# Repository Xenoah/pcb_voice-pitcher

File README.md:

# Voice Pitcher — standalone audio DSP prototype

**98 × 98 mm、表面のみの部品実装、SSD1306表示器と4つの操作ボタンを備えた音声エフェクターの設計・ファームウェアです。** STM32H743とPCM3060を使い、ステレオライン入出力とUSB-Cオーディオを切り替えます。

現在は **Rev 0.1の未実機検証プロトタイプ** です。回路図ERC・基板DRC・未接続はすべて0件、回路図とPCBの端子接続も照合済みです。実機の起動、USB互換性、音質、遅延、消費電流、温度は未測定です。添付データは試作レビュー用で、量産承認済みではありません。

## ダウンロード

- [全データ ZIP](downloads/voice_pitcher_rev0.1_prototype.zip?raw=true) — 回路図、PCB、製造データ、ファームウェア、説明書、検証記録
- [ガーバー・ドリル ZIP](downloads/voice_pitcher_gerbers.zip?raw=true)
- [JLCPCB用 BOM](downloads/jlc_bom.csv?raw=true) / [CPL](downloads/jlc_cpl.csv?raw=true) / [調達状況付き全BOM](downloads/bom_master.csv?raw=true)
- [日本語説明書 PDF](downloads/voice_pitcher_manual_ja.pdf?raw=true) / [回路図 PDF](downloads/schematic.pdf?raw=true) / [表面実装図 PDF](downloads/assembly-top.pdf?raw=true)
- [ファームウェア BIN](downloads/firmware/voice_pitcher.bin?raw=true) / [HEX](downloads/firmware/voice_pitcher.hex?raw=true) / [ELF](downloads/firmware/voice_pitcher.elf?raw=true)
- [検証結果](downloads/reports/hardware.json) / [DSP周波数テスト](downloads/reports/dsp-spectral.json) / [SHA-256](downloads/SHA256SUMS.txt)
- [スクリーンショット全18枚 ZIP](downloads/voice_pitcher_screenshots.zip?raw=true) / [画像付きプレリリース](https://github.com/Xenoah/pcb_voice-pitcher/releases/tag/v0.1.0-prototype)

CSVはページ右上のDownload raw file、ZIPは上記リンクから保存できます。BOMの空欄LCSC番号は未確定部品です。注文前に [製造手順](docs/manufacturing.md) の照合が必要です。

## スクリーンショット

実際のKiCadデータとPDFから出力した設計画面です。実機写真ではありません。3Dモデル未提供のJ1（USB-C）、J2/J3（音声ジャック）、Y1（発振器）、および外付けOLEDは3D表示に含まれません。

**3D斜視** — 98 × 98 mm、全ての部品を表面に実装する設計。

**表裏・4層の一覧** — 上段は3D表裏、中段は表裏配線、下段はGND / 3.3 V内層。裏面図は裏側から見た向きです。

**回路図全7ページと説明書** — 全体構成、MCU、電源、USB、コーデック、アナログ、表示・操作回路。

<details>
<summary>個別の高解像度画像を表示</summary>

|3D表面|3D裏面|
|---|---|
|||
|表面配線|裏面配線|
|||
|L2 GND|L3 3.3 V|
|||
|実装図|回路図：全体|
|||
|回路図：MCU|回路図：電源|
|||
|回路図：USB-C|回路図：コーデック|
|||
|回路図：アナログ|回路図：OLED・スイッチ|
|||
|日本語説明書・先頭ページ|画像の生成元|
||[CADハッシュ・3Dモデル出典・画像一覧](downloads/screenshots/manifest.json)|

</details>

画像を再生成する場合は `python3 tools/render_gallery.py --fetch-models` を実行します。KiCad 9、Inkscape、poppler-utils、Python Pillow/reportlabが必要です。

## 設計内容

|項目|Rev 0.1の内容|
|---|---|
|基板|98 × 98 mm、4層、部品は全てTOP。片面実装であり、片面銅箔基板ではありません|
|処理|STM32H743VIT6、400 MHz、32 bit float DSP、24 bit / 48 kHzステレオ|
|変換|PCM3060PWR、独立したADC/DAC、アナログ5 V・デジタル3.3 V|
|アナログ端子|入力・出力各1個の3.5 mm TRSステレオライン。6.35 mmは外付け変換アダプタ|
|USB-C|USB 2.0 Full Speed、UAC2のデバイス。PC・スマホ側がホスト|
|ルーティング|LINE→LINE、LINE→USB、USB→LINE、USB→USB|
|操作|SSD1306 128×64 I²C、MODE / DOWN / UP / I/O、別途RESET / BOOT|
|エフェクト|DRY、±12半音ピッチ変更、単音ピッチ補正、500 msディレイ、5 Hzトレモロ|
|スタンドアローン|PC不要のLINE→LINE動作。5 Vで1.5 A以上を広告するType-C電源を想定|
|調達|抵抗と100 nFを中心にJLCPCB Basicへ寄せた構成。全品Basicではありません|

**ピッチ変更を「音質ロスゼロ・遅延ゼロ」で行うことはできません。** 音程推定には観測時間が必要で、ADC/DAC・バッファにも遅延があります。本設計は専用基板上のMCUでリアルタイム処理します。無加工デジタルDRYは24 bit整数の往復一致をテスト済みですが、アナログ往復やピッチ処理の無損失を意味しません。

DRYのアナログ往復は計算上約2.1 msを起点とする設計です。ピッチ処理は可変遅延約1.3–65.3 ms、音程検出は約42.7 msの窓に分割演算と追従時間が加わります。USB経路はさらにホストのバッファに依存します。いずれも実測保証値ではありません。

## 使い方と設計資料

1. [ハードウェア仕様・ピン配置](docs/hardware.md)
2. [ファームウェア・操作・ビルド](docs/firmware.md)
3. [JLCPCB製造・部品調達](docs/manufacturing.md)
4. [検証済み範囲と実機チェック](docs/validation.md)
5. [データシートと依存ライブラリ](docs/sources.md)

通常のマイク、パッシブギター、ヘッドホンを直接つなぐための回路ではありません。マイクには外部プリアンプ、楽器には適切なバッファ、ヘッドホンには外部アンプを使用してください。USBホスト機能はないため、別のUSBオーディオインターフェースを本機へ直接接続する構成には対応しません。

KiCad 9で [hardware/voice_pitcher.kicad_pro](hardware/voice_pitcher.kicad_pro) を開けます。配線済みPCBは `voice_pitcher.kicad_pcb` です。`placement.kicad_pcb` は再配置・再配線用の中間ファイルです。

```sh
bash tools/bootstrap.sh
make test
make firmware
make hardware-check
make exports
python3 tools/package_release.py
```

必要なツールとインストール方法は [ビルド手順](docs/firmware.md) を参照してください。オリジナルコード・設計はMIT、同梱KiCadライブラリと外部依存物にはそれぞれのライセンスが適用されます。

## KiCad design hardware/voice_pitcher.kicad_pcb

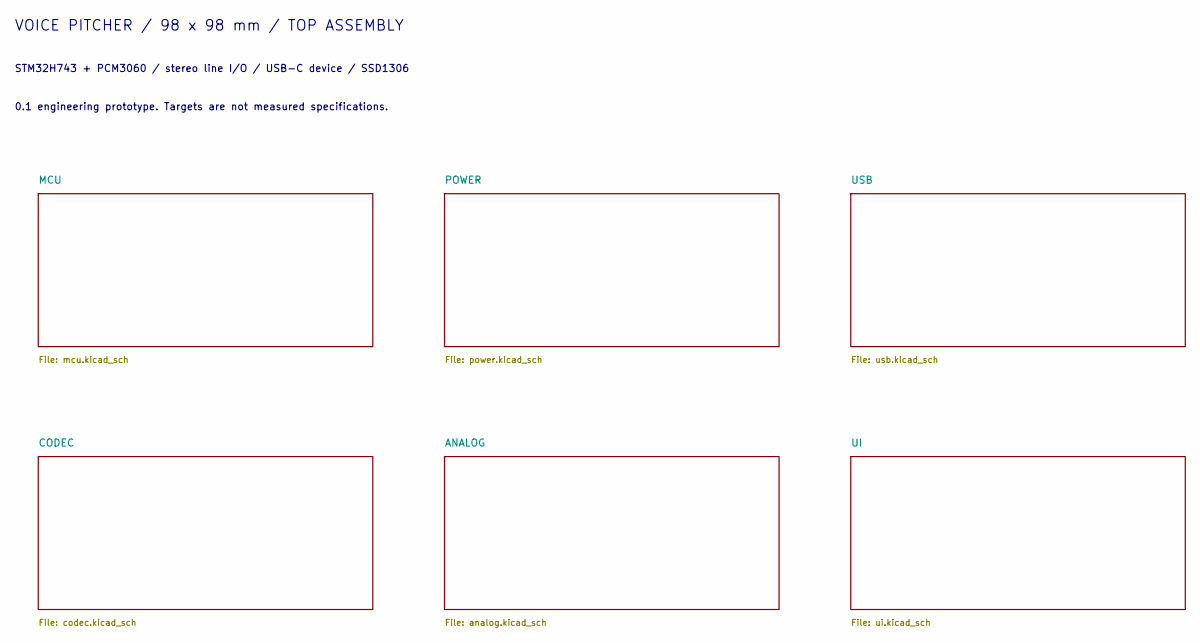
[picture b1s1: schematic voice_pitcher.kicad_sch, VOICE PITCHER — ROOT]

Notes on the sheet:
VOICE PITCHER / 98 x 98 mm / TOP ASSEMBLY
STM32H743 + PCM3060 / stereo line I/O / USB-C device / SSD1306
0.1 engineering prototype. Targets are not measured specifications.

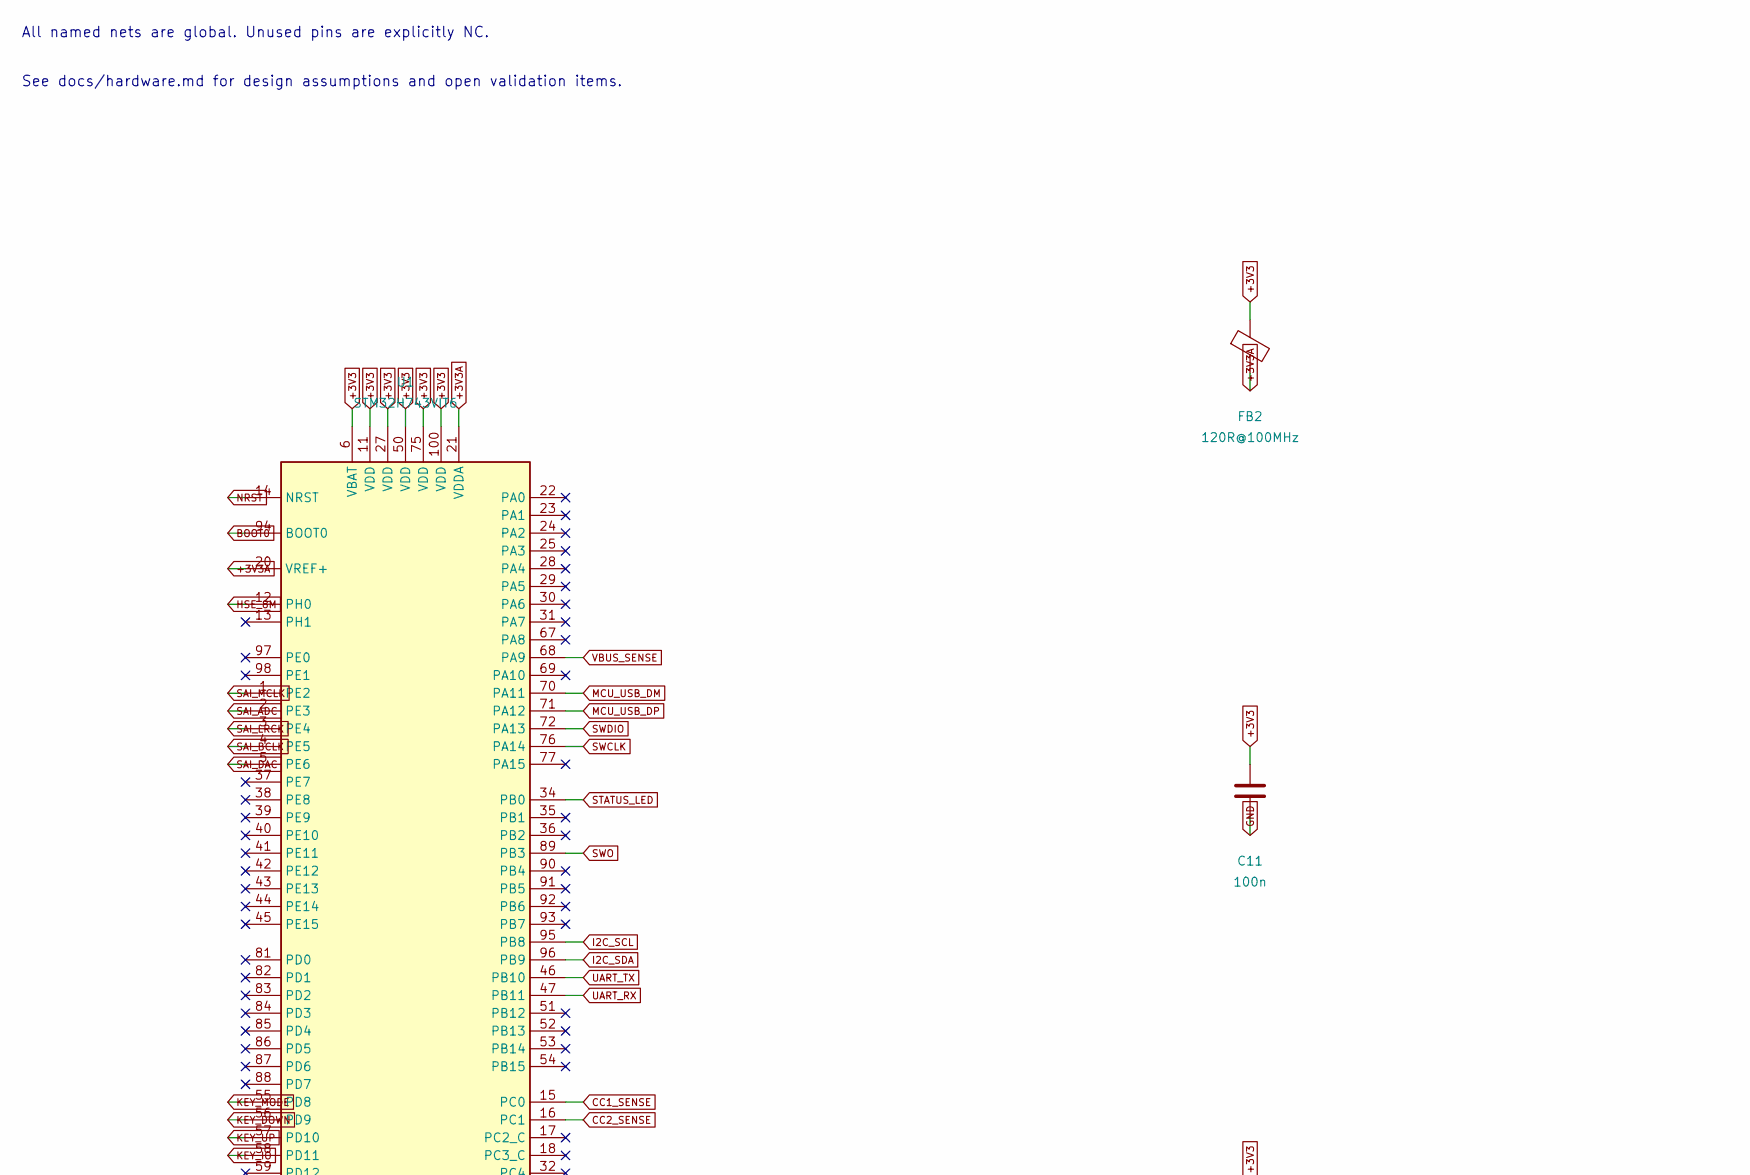
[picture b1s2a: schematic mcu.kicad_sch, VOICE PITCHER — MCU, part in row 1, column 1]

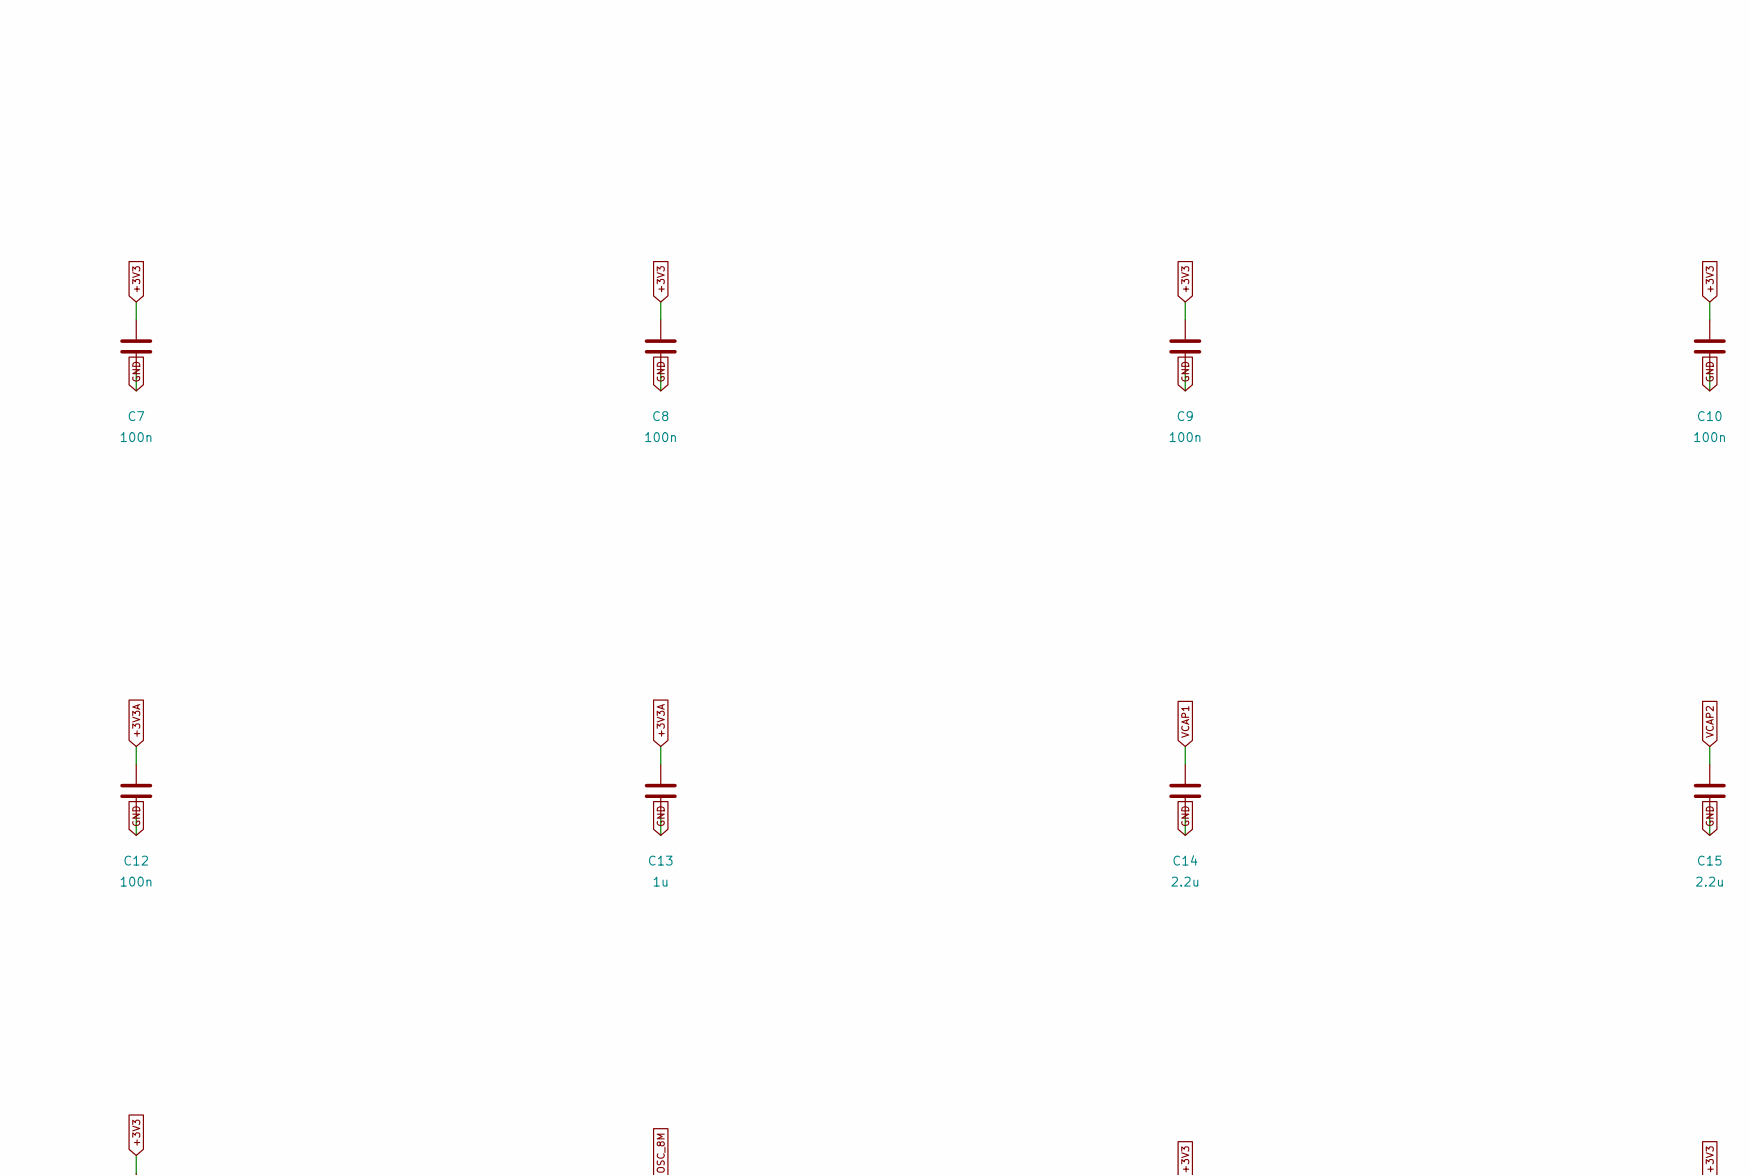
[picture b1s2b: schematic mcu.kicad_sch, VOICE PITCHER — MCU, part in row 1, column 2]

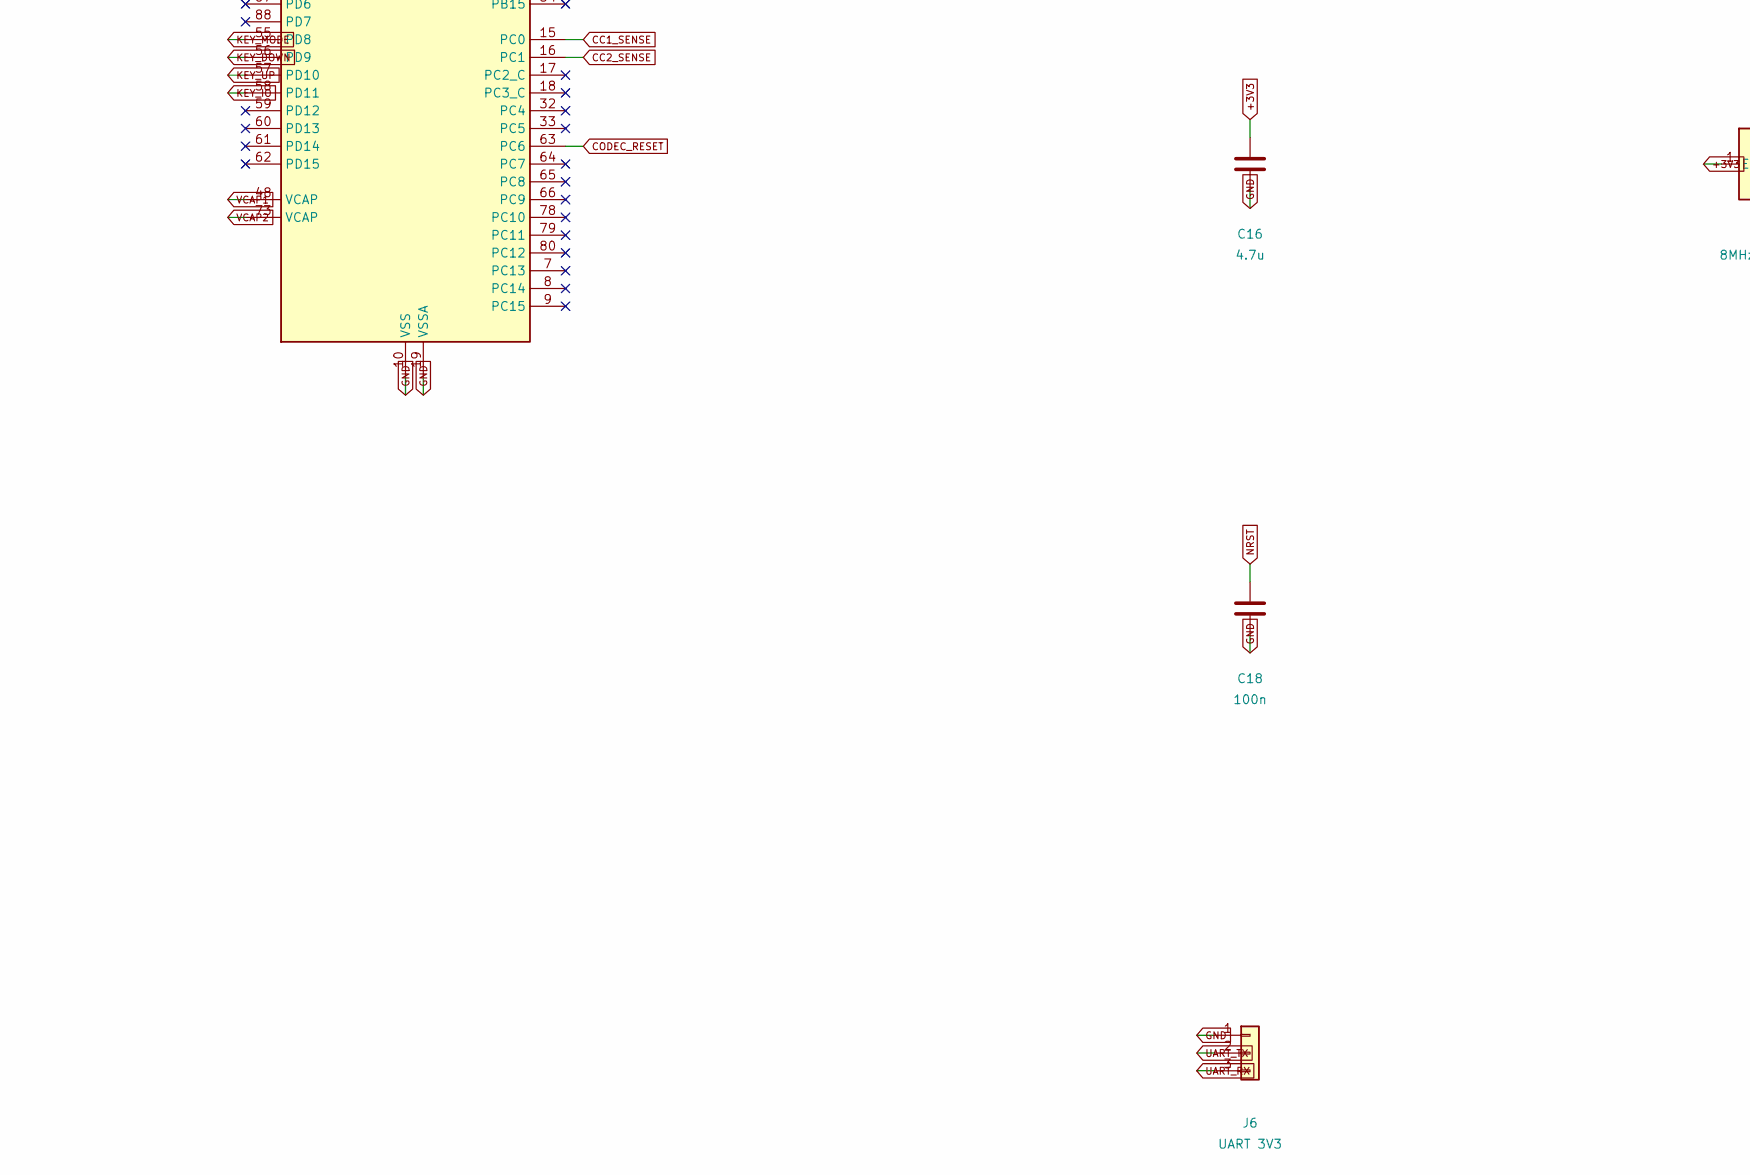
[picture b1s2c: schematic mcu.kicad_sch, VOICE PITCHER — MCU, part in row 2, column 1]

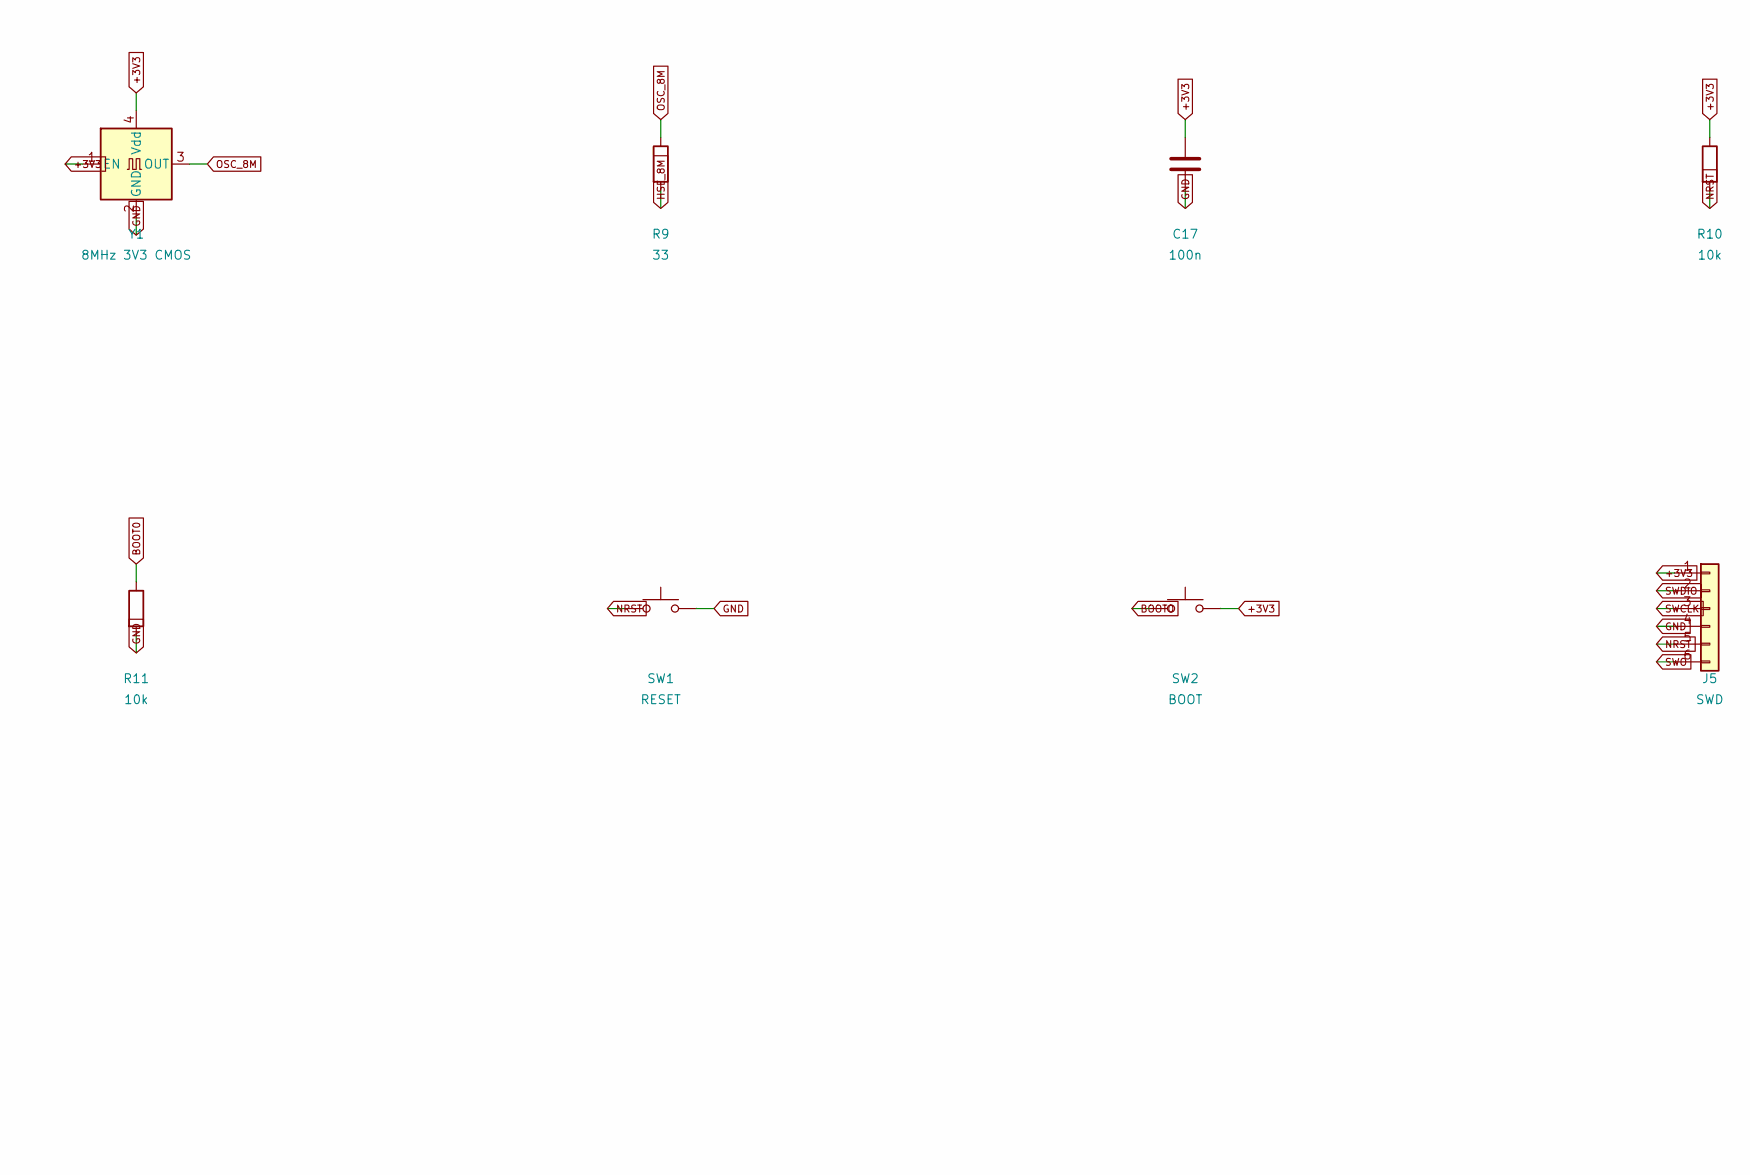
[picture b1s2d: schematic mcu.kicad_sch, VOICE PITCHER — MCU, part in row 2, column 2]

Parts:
C7, C8, C9, C10, C11, C12, C17, C18: 100n; Capacitor_SMD__C_0603_1608Metric; MPN CC0603KRX7R9BB104; LCSC C14663
C13: 1u; Capacitor_SMD__C_0603_1608Metric; MPN GRM188R71C105KA12D
C14, C15: 2.2u; Capacitor_SMD__C_0603_1608Metric; MPN GRM188R61C225KE15D
C16: 4.7u; Capacitor_SMD__C_0603_1608Metric; MPN GRM188R61C475KE11D
FB2: 120R@100MHz; Inductor_SMD__L_0805_2012Metric; MPN BLM21PG121SN1D
J5: SWD; Connector_PinHeader_2.54mm__PinHeader_1x06_P2.54mm_Vertical; MPN 1x6 2.54mm header
J6: UART 3V3; Connector_PinHeader_2.54mm__PinHeader_1x03_P2.54mm_Vertical; MPN 1x3 2.54mm header
R9: 33; Resistor_SMD__R_0603_1608Metric; MPN 0603WAF330JT5E; LCSC C23140
R10, R11: 10k; Resistor_SMD__R_0603_1608Metric; MPN 0603WAF1002T5E; LCSC C25804
SW1: RESET; Button_Switch_SMD__SW_SPST_TL3342; MPN TL3342F160QG
SW2: BOOT; Button_Switch_SMD__SW_SPST_TL3342; MPN TL3342F160QG
U1: STM32H743VIT6; Package_QFP__LQFP-100_14x14mm_P0.5mm; MPN STM32H743VIT6; LCSC C114409
Y1: 8MHz 3V3 CMOS; Oscillator__Oscillator_SMD_Abracon_ASE-4Pin_3.2x2.5mm; MPN ASE-8.000MHZ-LC-T

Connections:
+3V3: C7.1, C8.1, C9.1, C10.1, C11.1, C16.1, C17.1, FB2.1, J5.1, R10.1, SW2.2, U1.6 (VBAT), U1.11 (VDD), U1.27 (VDD), U1.50 (VDD), U1.75 (VDD), U1.100 (VDD), Y1.1 (EN), Y1.4 (Vdd); also elsewhere on the board
+3V3A: C12.1, C13.1, FB2.2, U1.20 (VREF+), U1.21 (VDDA)
BOOT0: R11.1, SW2.1, U1.94 (BOOT0)
CC1_SENSE: U1.15 (PC0); also elsewhere on the board
CC2_SENSE: U1.16 (PC1); also elsewhere on the board
CODEC_RESET: U1.63 (PC6); also elsewhere on the board
GND: C7.2, C8.2, C9.2, C10.2, C11.2, C12.2, C13.2, C14.2, C15.2, C16.2, C17.2, C18.2, J5.4, J6.1, R11.2, SW1.2, U1.10 (VSS), U1.19 (VSSA), U1.26 (VSS), U1.49 (VSS), U1.74 (VSS), U1.99 (VSS), Y1.2 (GND); also elsewhere on the board
HSE_8M: R9.2, U1.12 (PH0)
I2C_SCL: U1.95 (PB8); also elsewhere on the board
I2C_SDA: U1.96 (PB9); also elsewhere on the board
KEY_DOWN: U1.56 (PD9); also elsewhere on the board
KEY_IO: U1.58 (PD11); also elsewhere on the board
KEY_MODE: U1.55 (PD8); also elsewhere on the board
KEY_UP: U1.57 (PD10); also elsewhere on the board
MCU_USB_DM: U1.70 (PA11); also elsewhere on the board
MCU_USB_DP: U1.71 (PA12); also elsewhere on the board
NRST: C18.1, J5.5, R10.2, SW1.1, U1.14 (NRST)
OSC_8M: R9.1, Y1.3 (OUT)
SAI_ADC: U1.2 (PE3); also elsewhere on the board
SAI_BCLK: U1.4 (PE5); also elsewhere on the board
SAI_DAC: U1.5 (PE6); also elsewhere on the board
SAI_LRCK: U1.3 (PE4); also elsewhere on the board
SAI_MCLK: U1.1 (PE2); also elsewhere on the board
STATUS_LED: U1.34 (PB0); also elsewhere on the board
SWCLK: J5.3, U1.76 (PA14)
SWDIO: J5.2, U1.72 (PA13)
SWO: J5.6, U1.89 (PB3)
UART_RX: J6.3, U1.47 (PB11)
UART_TX: J6.2, U1.46 (PB10)
VBUS_SENSE: U1.68 (PA9); also elsewhere on the board
VCAP1: C14.1, U1.48 (VCAP)
VCAP2: C15.1, U1.73 (VCAP)

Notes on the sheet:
All named nets are global. Unused pins are explicitly NC.
See docs/hardware.md for design assumptions and open validation items.

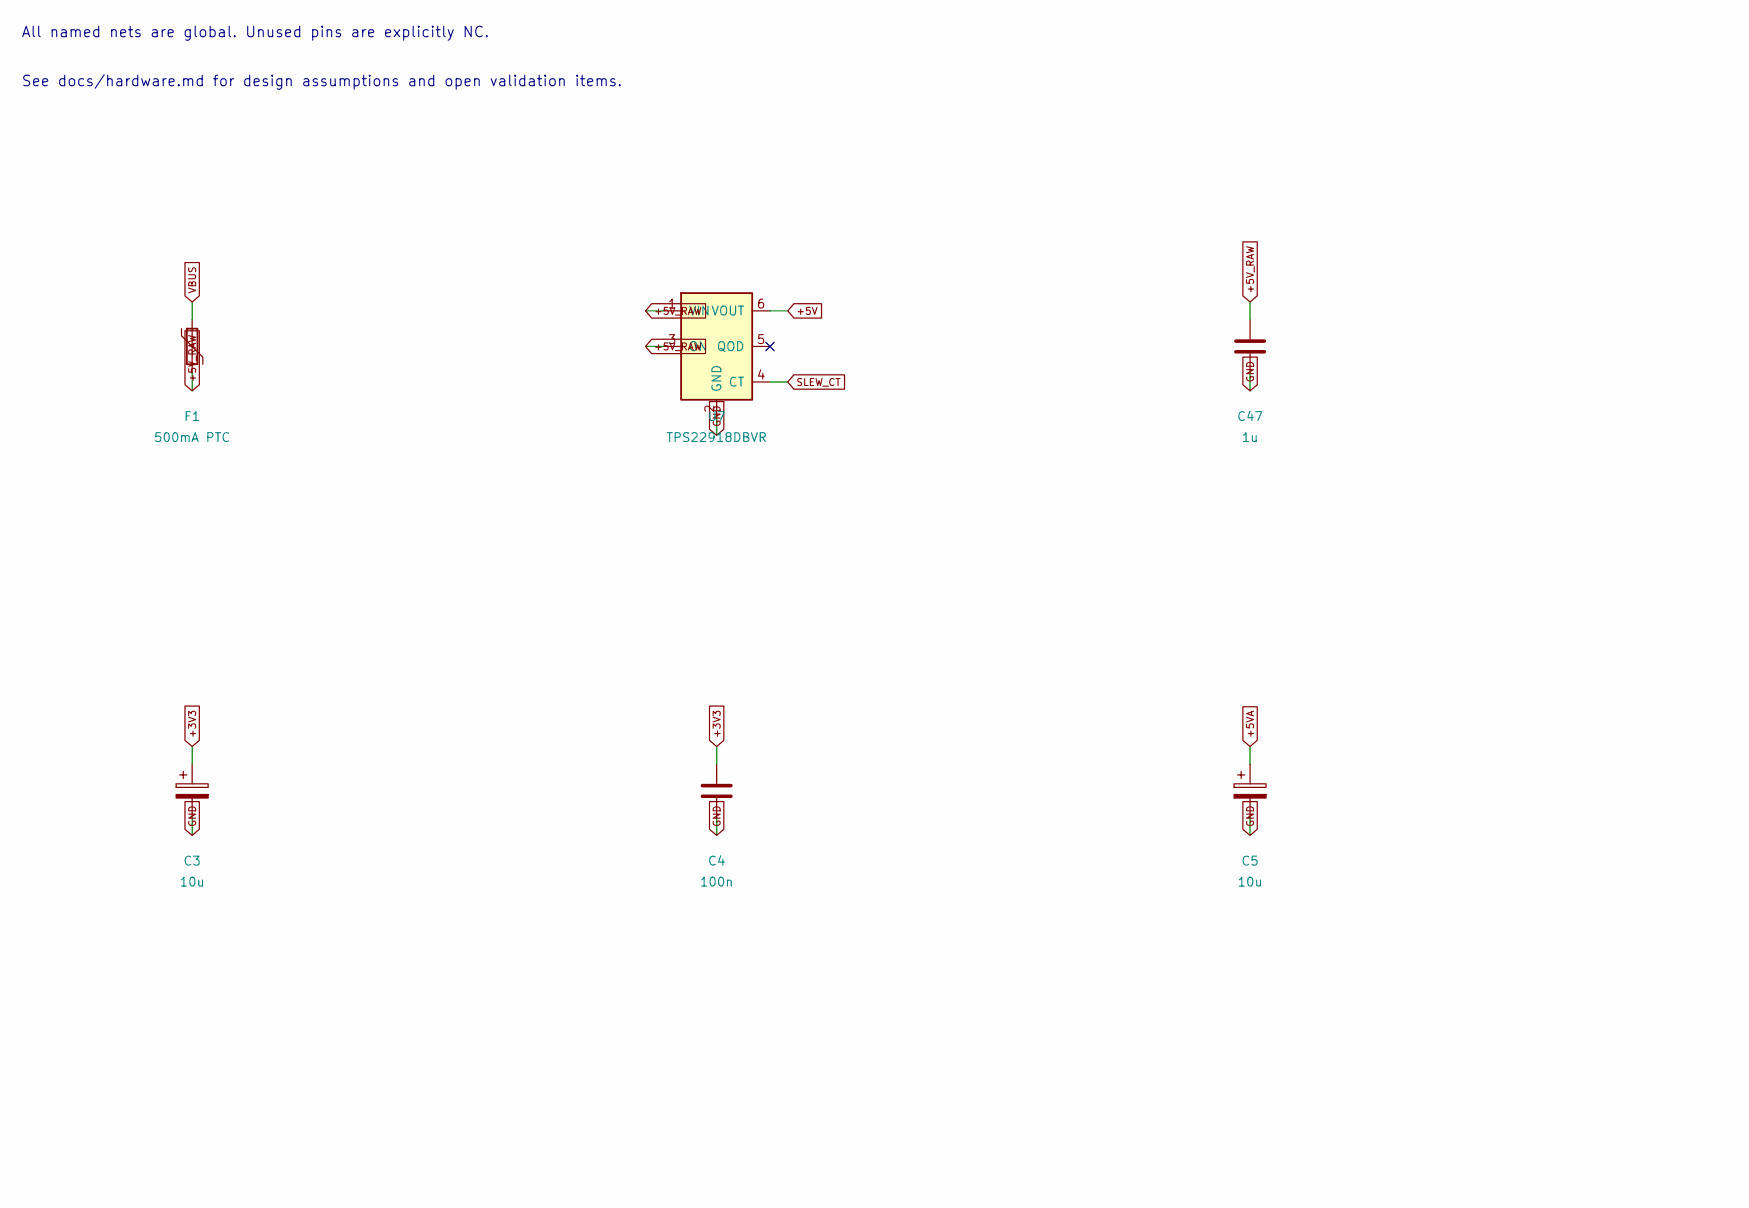
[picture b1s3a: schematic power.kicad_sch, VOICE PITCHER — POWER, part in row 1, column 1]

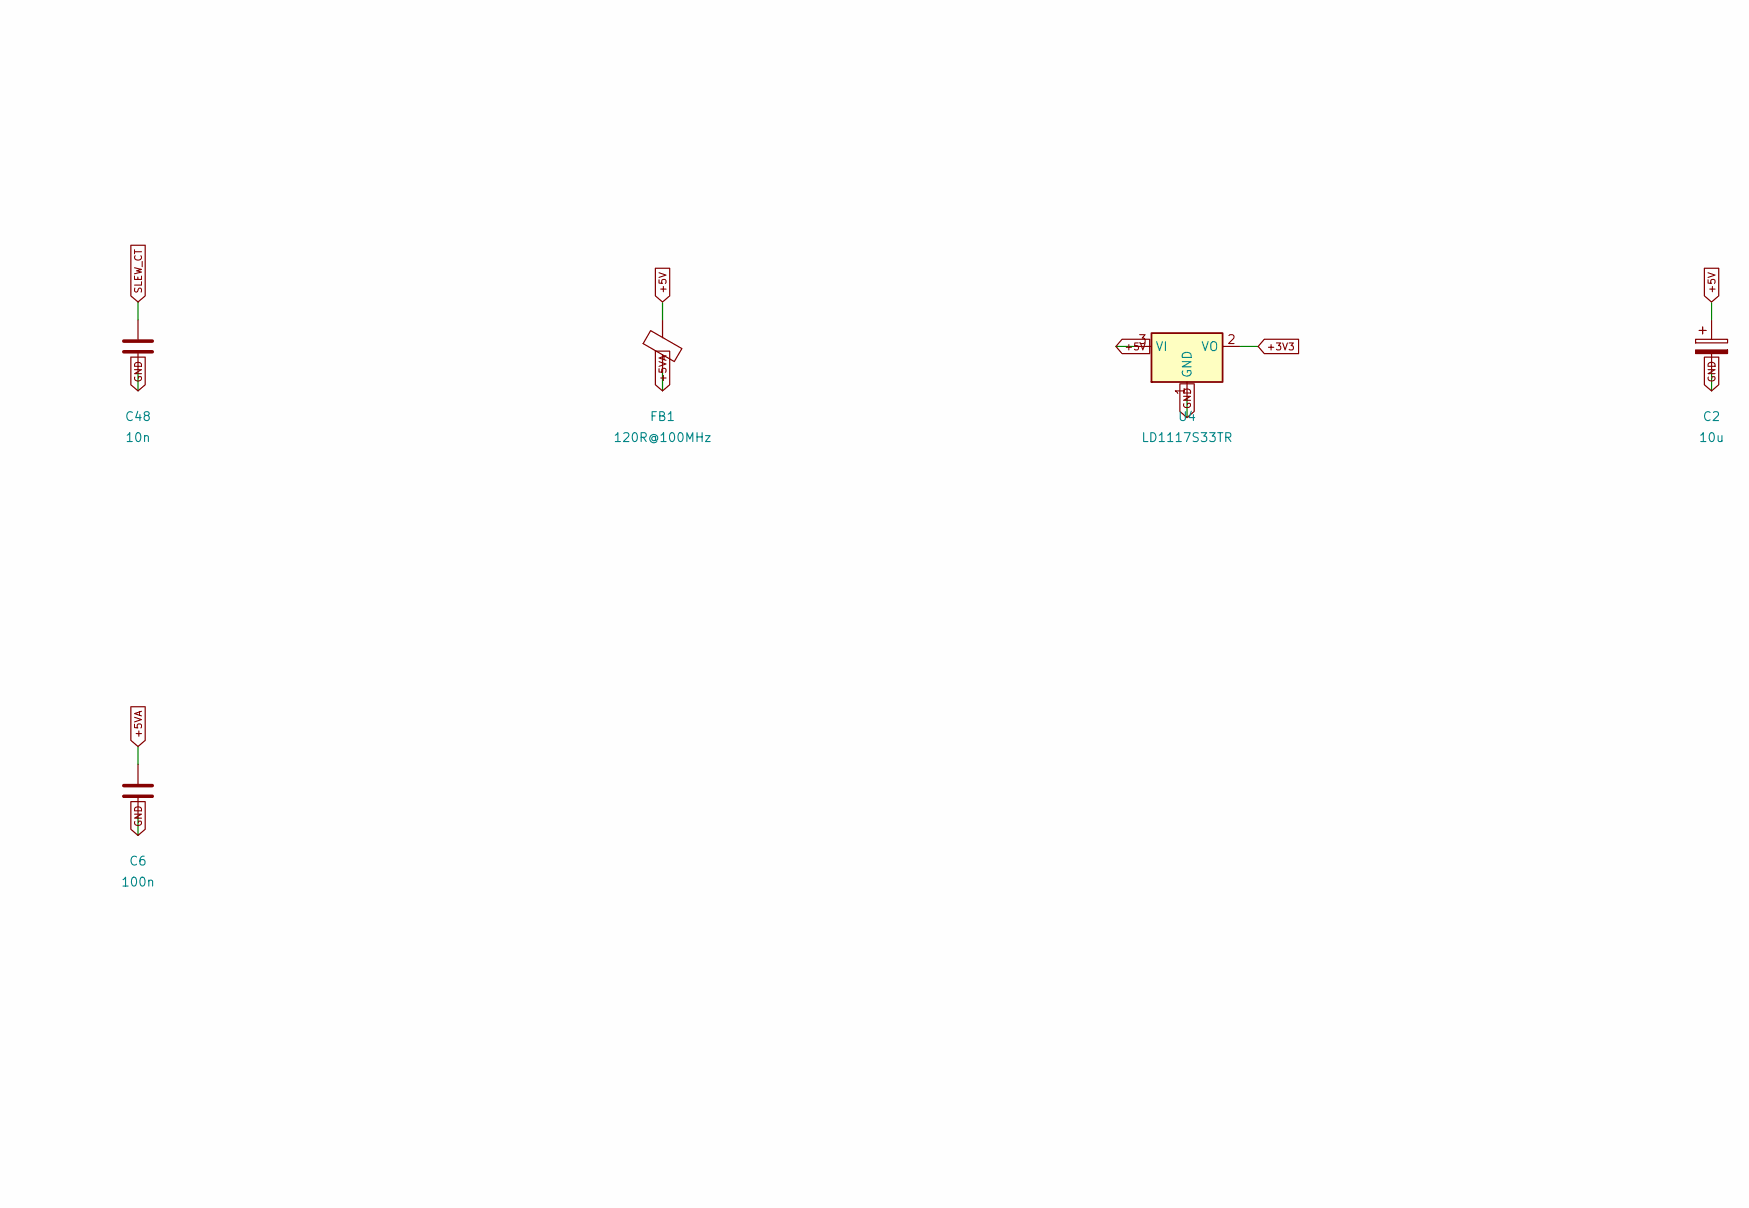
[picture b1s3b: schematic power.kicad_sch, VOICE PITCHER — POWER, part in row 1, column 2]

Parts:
C2, C3, C5: 10u; Capacitor_SMD__CP_Elec_4x5.8; MPN UWT1C100MCL1GB
C4, C6: 100n; Capacitor_SMD__C_0603_1608Metric; MPN CC0603KRX7R9BB104; LCSC C14663
C47: 1u; Capacitor_SMD__C_0603_1608Metric; MPN GRM188R71C105KA12D
C48: 10n; Capacitor_SMD__C_0603_1608Metric; MPN GRM188R71E103KA01D
F1: 500mA PTC; Fuse__Fuse_1206_3216Metric; MPN 1206L050YR
FB1: 120R@100MHz; Inductor_SMD__L_0805_2012Metric; MPN BLM21PG121SN1D
U4: LD1117S33TR; Package_TO_SOT_SMD__SOT-223-3_TabPin2; MPN LD1117S33TR
U7: TPS22918DBVR; Package_TO_SOT_SMD__SOT-23-6; MPN TPS22918DBVR

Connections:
+3V3: C3.1, C4.1, U4.2 (VO); also elsewhere on the board
+5V: C2.1, FB1.1, U4.3 (VI), U7.6 (VOUT)
+5VA: C5.1, C6.1, FB1.2; also elsewhere on the board
+5V_RAW: C47.1, F1.2, U7.1 (VIN), U7.3 (ON)
GND: C2.2, C3.2, C4.2, C5.2, C6.2, C47.2, C48.2, U4.1 (GND), U7.2 (GND); also elsewhere on the board
SLEW_CT: C48.1, U7.4 (CT)
VBUS: F1.1; also elsewhere on the board

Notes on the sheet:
All named nets are global. Unused pins are explicitly NC.
See docs/hardware.md for design assumptions and open validation items.

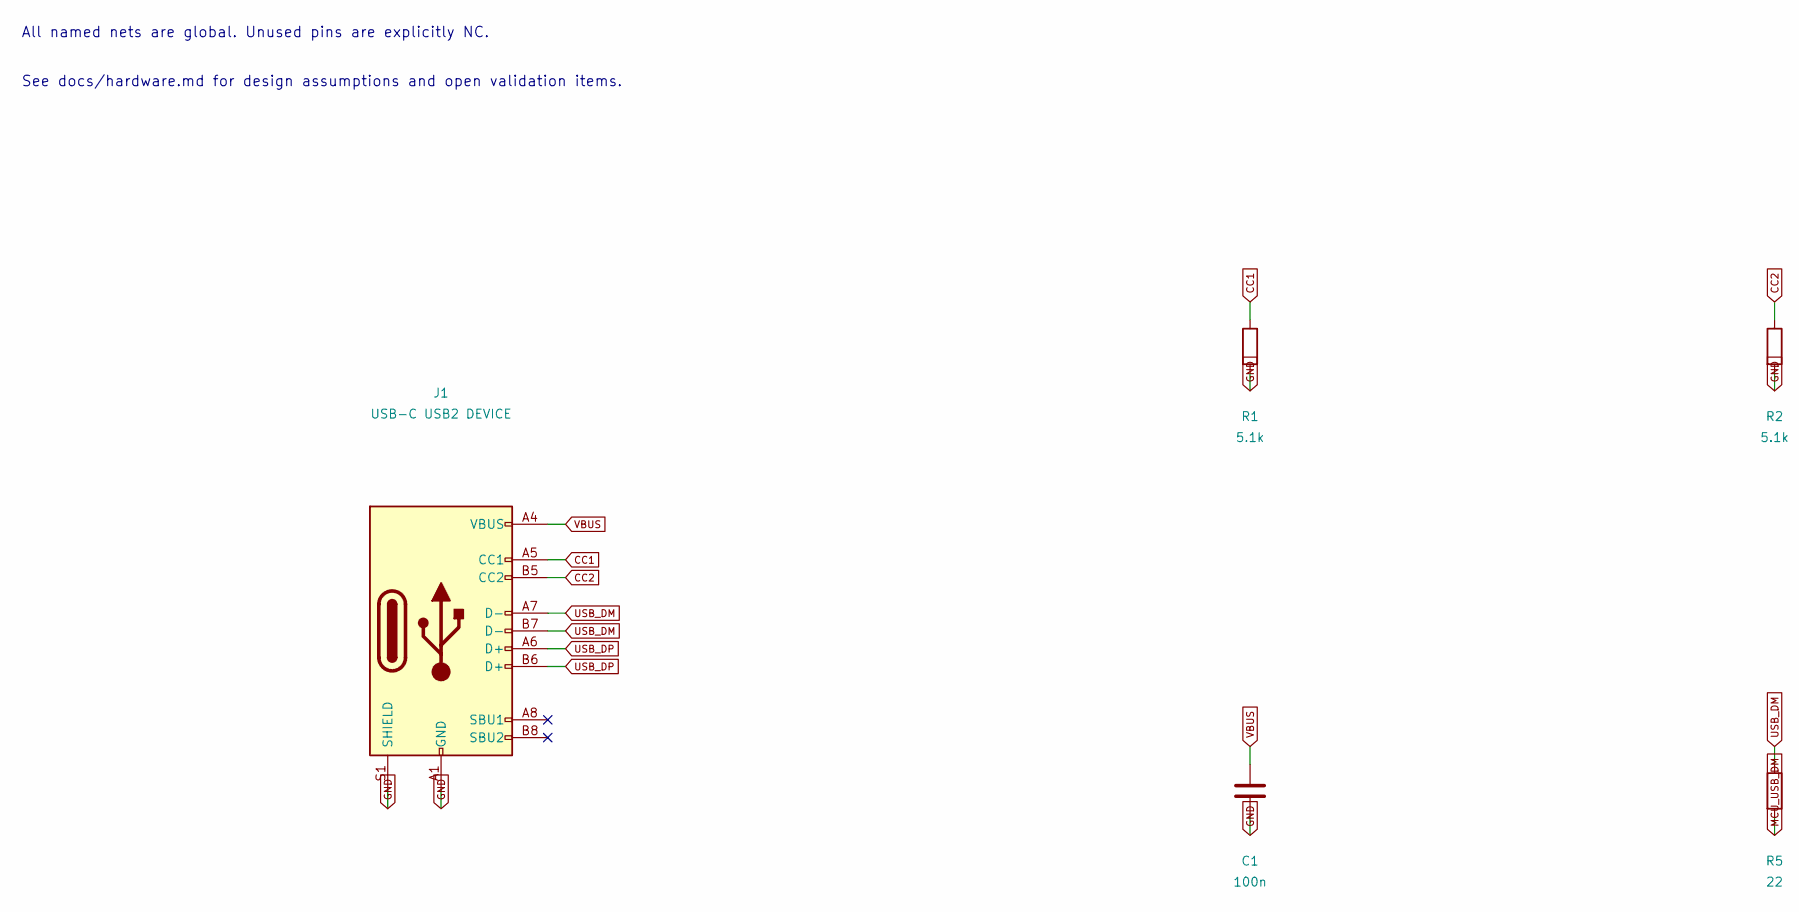
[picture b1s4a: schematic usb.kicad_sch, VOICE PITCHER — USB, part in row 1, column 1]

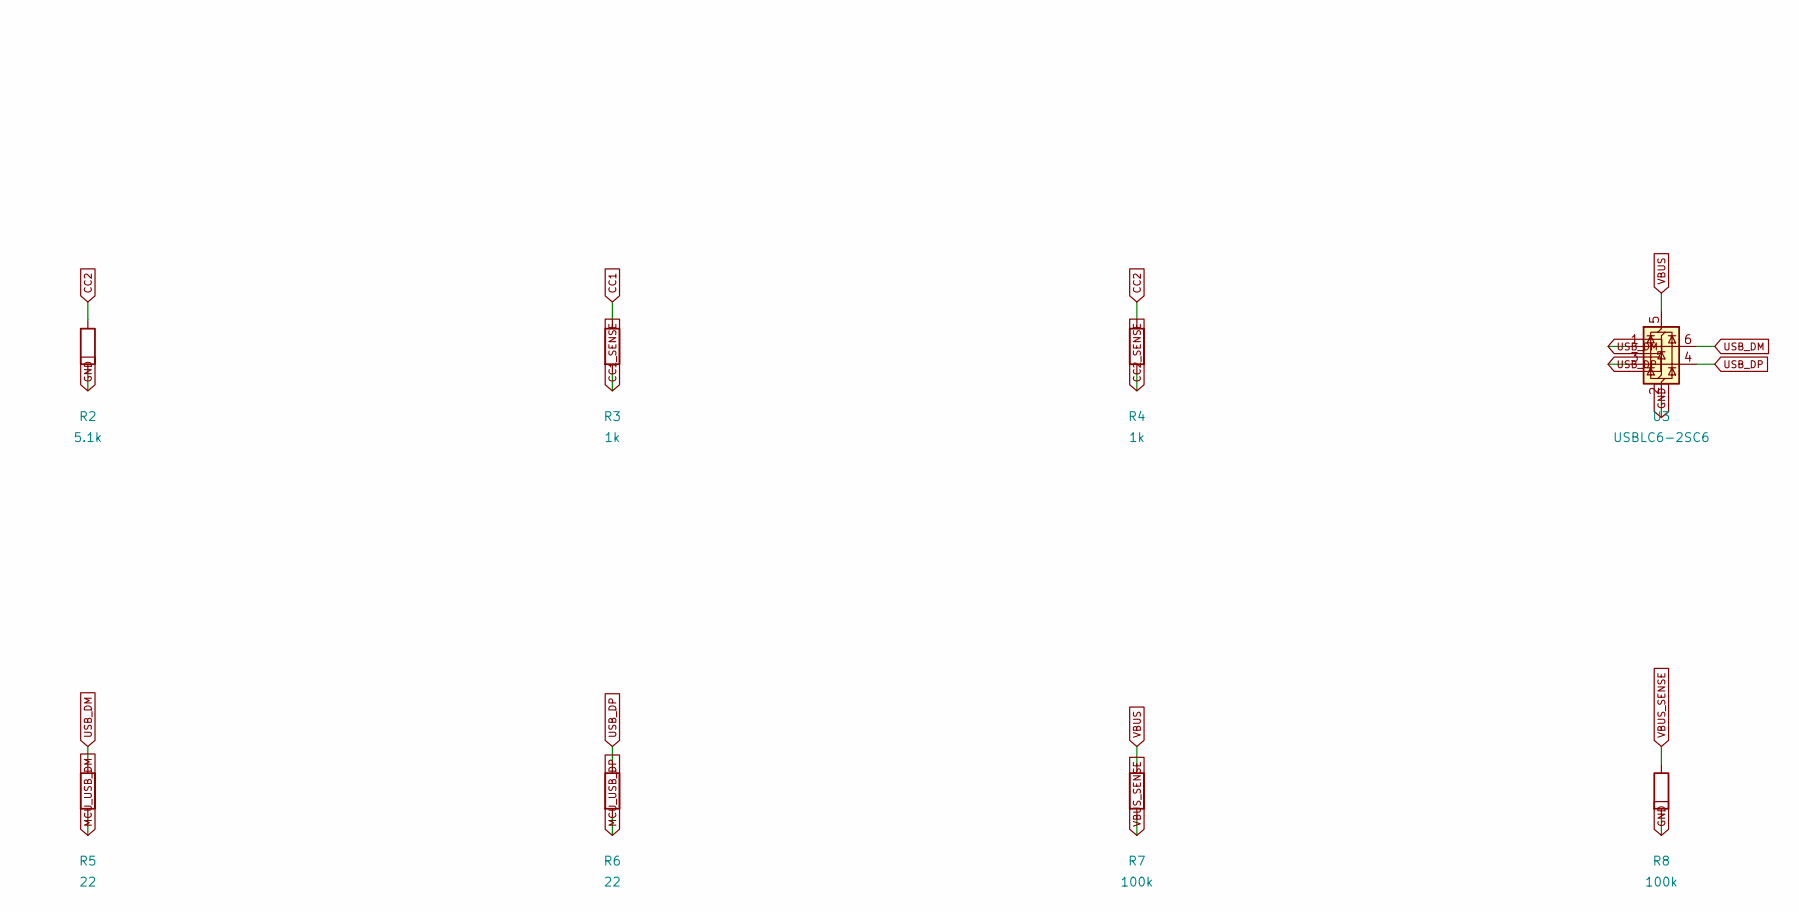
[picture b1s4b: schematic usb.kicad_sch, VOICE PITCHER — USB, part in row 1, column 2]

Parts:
C1: 100n; Capacitor_SMD__C_0603_1608Metric; MPN CC0603KRX7R9BB104; LCSC C14663
J1: USB-C USB2 DEVICE; Connector_USB__USB_C_Receptacle_HRO_TYPE-C-31-M-12; MPN TYPE-C-31-M-12; LCSC C165948
R1, R2: 5.1k; Resistor_SMD__R_0603_1608Metric; MPN 0603WAF5101T5E; LCSC C23186
R3, R4: 1k; Resistor_SMD__R_0603_1608Metric; MPN 0603WAF1001T5E; LCSC C21190
R5, R6: 22; Resistor_SMD__R_0603_1608Metric; MPN 0603WAF220JT5E; LCSC C23345
R7, R8: 100k; Resistor_SMD__R_0603_1608Metric; MPN 0603WAF1003T5E; LCSC C25803
U3: USBLC6-2SC6; Package_TO_SOT_SMD__SOT-23-6; MPN USBLC6-2SC6; LCSC C7519

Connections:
CC1: J1.A5 (CC1), R1.1, R3.1
CC1_SENSE: R3.2; also elsewhere on the board
CC2: J1.B5 (CC2), R2.1, R4.1
CC2_SENSE: R4.2; also elsewhere on the board
GND: C1.2, J1.A1 (GND), J1.A12 (GND), J1.B1 (GND), J1.B12 (GND), J1.S1 (SHIELD), R1.2, R2.2, R8.2, U3.2 (GND); also elsewhere on the board
MCU_USB_DM: R5.2; also elsewhere on the board
MCU_USB_DP: R6.2; also elsewhere on the board
USB_DM: J1.A7 (D-), J1.B7 (D-), R5.1, U3.1 (I/O1), U3.6 (I/O1)
USB_DP: J1.A6 (D+), J1.B6 (D+), R6.1, U3.3 (I/O2), U3.4 (I/O2)
VBUS: C1.1, J1.A4 (VBUS), J1.A9 (VBUS), J1.B4 (VBUS), J1.B9 (VBUS), R7.1, U3.5 (VBUS); also elsewhere on the board
VBUS_SENSE: R7.2, R8.1; also elsewhere on the board

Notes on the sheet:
All named nets are global. Unused pins are explicitly NC.
See docs/hardware.md for design assumptions and open validation items.
